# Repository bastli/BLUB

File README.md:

BLUB
====

https://people.ee.ethz.ch/~bastli/wiki/index.php?title=BLUB

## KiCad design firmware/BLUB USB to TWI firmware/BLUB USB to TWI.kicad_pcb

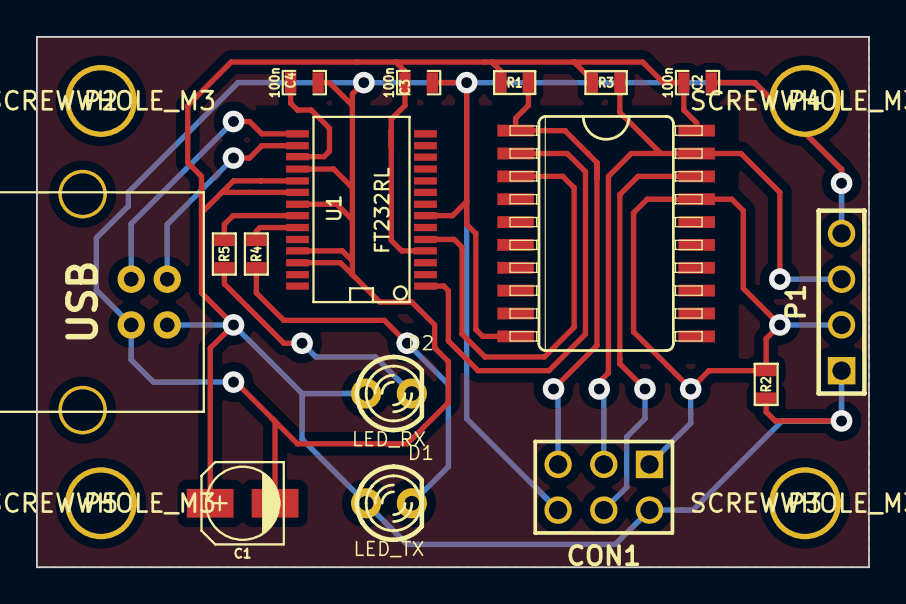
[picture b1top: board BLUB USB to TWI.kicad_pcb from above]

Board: 2 copper layers, 46.2 x 29.5 mm, 20 parts (0 on the bottom side), 15 nets.

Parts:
C1: 4u7; c_elec_4x5.7
C2, C3, C4: 100n; SM0603_Capa
CON1: AVR-ISP-6; pin_array_3x2
D1: LED_TX; LED-3MM
D2: LED_RX; LED-3MM
IC1: ATTINY2313-S; tmc-SOIC20
J1: USB; USB_B
P1: TWI; PIN_ARRAY_4x1
P2, P3, P4, P5: SCREWWHOLE_M3
R1: R; SM0603
R2, R3: 2k; SM0603
R4, R5: 270; SM0603
U1: FT232RL; SSOP28

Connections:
D+: J1.3, U1.15
D-: J1.2, U1.16
GND: C1.2, C2.2, C3.2, C4.2, CON1.6, IC1.10, J1.4, P1.4, U1.7, U1.18, U1.21, U1.25, U1.26
LED_RX: R5.2, U1.22
LED_TX: R4.2, U1.23
MISO: CON1.4, IC1.18
MOSI: CON1.1, IC1.17, P1.2, R2.2
unnamed: C4.1, U1.17
unnamed: D1.2, R4.1
unnamed: D2.2, R5.1
RST: CON1.5, IC1.1, R1.2
RXD: IC1.2, U1.1
SCK: CON1.3, IC1.19, P1.3, R3.2
TXD: IC1.3, U1.5
VCC: C1.1, C2.1, C3.1, CON1.2, D1.1, D2.1, IC1.20, J1.1, P1.1, R1.1, R2.1, R3.1, U1.4, U1.19, U1.20

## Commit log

2013-10-16 Add firmware and GUI test code by Lukas.
2013-10-18 Add drawing app
2013-10-18 Fix Readme
2013-10-18 Running example
2013-10-19 Add bootstrap, paper.js and basic scaffold.
2013-10-20 Add new code by Lukas. New code for web front-end by Kusi.
2013-10-23 Draw some bubbles
2013-10-25 remove legacy comment
2013-10-25 all the graphics
2013-10-26 test commit
2013-11-13 first functional prototype
2013-11-13 Stable prototype
2013-11-13 Some minor changes to tcp error handling for more robust server.
2013-11-14 some production adaptions
2013-11-14 Only try to reconnect to server each 10s
2013-11-14 fix package.json file to allow for autoinstall
2013-11-14 first implementation of buffer-offsetting for testing
2013-11-14 Test code for buffer_offsetting
2013-11-14 adapt values
2013-11-14 comment out debug code safely
2014-09-26 Add BLUBmotion interface server to repository
